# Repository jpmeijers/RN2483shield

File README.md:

# RN2483shield
KiCad design for a RN2483 shield for the Arduino Uno

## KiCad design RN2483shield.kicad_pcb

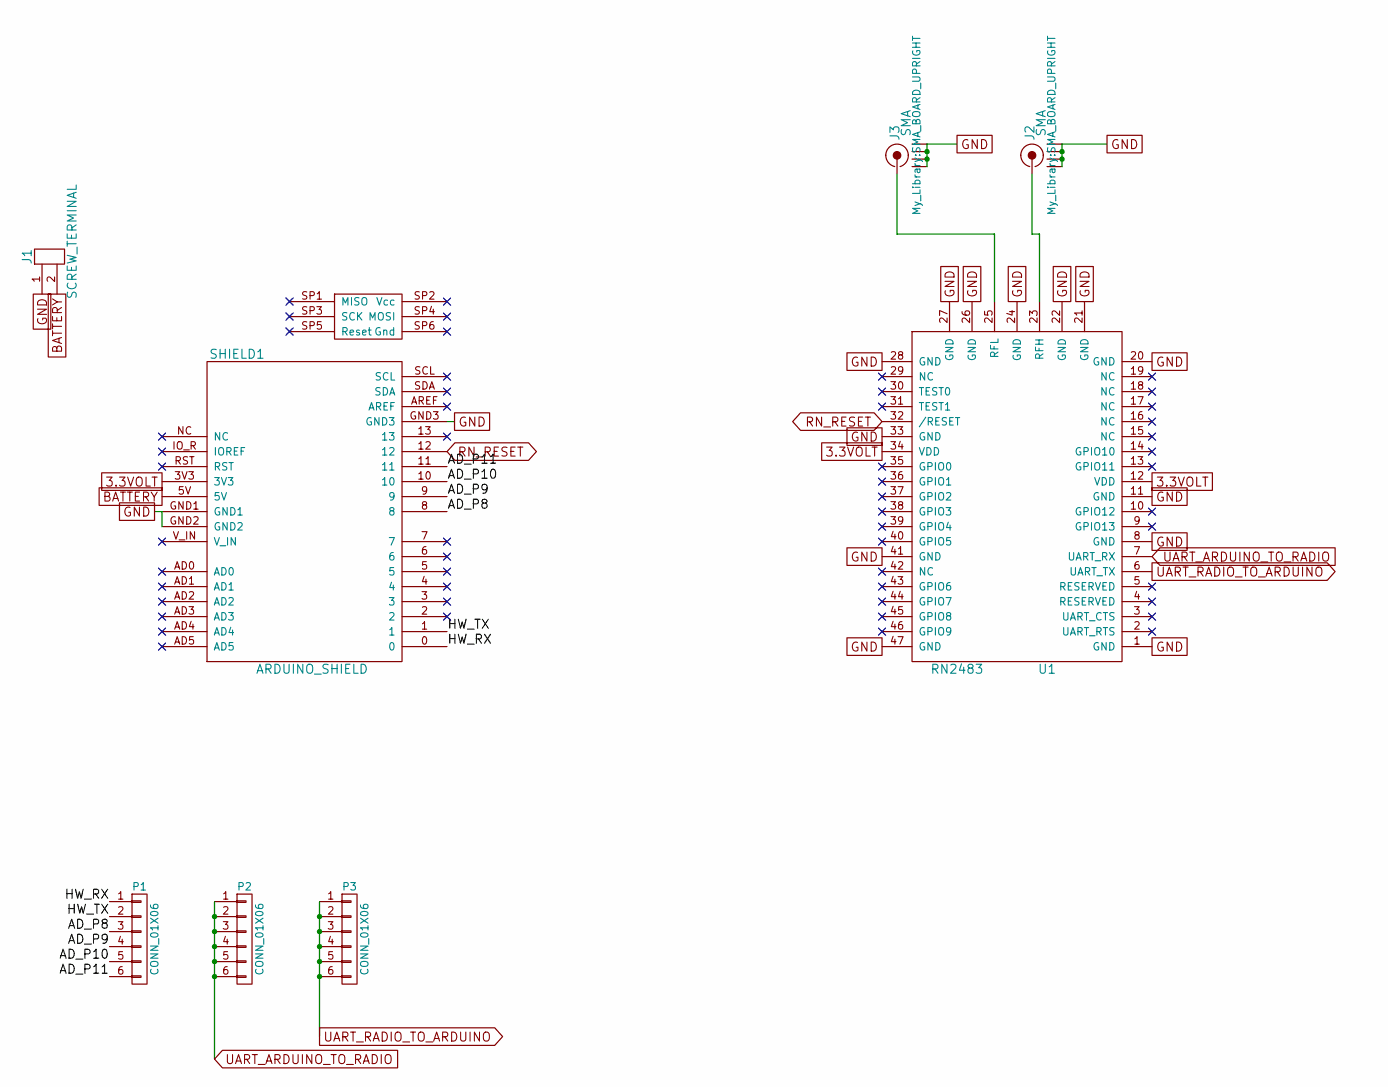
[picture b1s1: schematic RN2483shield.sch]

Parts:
J1: SCREW_TERMINAL; SCREWTERMINAL-5MM-2
J2, J3: SMA; SMA_BOARD_UPRIGHT
P1, P2, P3: CONN_01X06; Socket_Strip_Straight_1x06
SHIELD1: ARDUINO_SHIELD
U1: RN2483

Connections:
3.3VOLT: SHIELD1.3V3, U1.12 (VDD), U1.34 (VDD)
/AD_P8: P1.3, SHIELD1.8
/AD_P9: P1.4, SHIELD1.9
/AD_P10: P1.5, SHIELD1.10
/AD_P11: P1.6, SHIELD1.11
/HW_RX: P1.1, SHIELD1.0
/HW_TX: P1.2, SHIELD1.1
BATTERY: J1.2, SHIELD1.5V
GND: J1.1, J2.2 (GND1), J2.3 (GND2), J2.4 (GND3), J2.5 (GND4), J3.2 (GND1), J3.3 (GND2), J3.4 (GND3), J3.5 (GND4), SHIELD1.GND1, SHIELD1.GND2, SHIELD1.GND3, U1.1 (GND), U1.8 (GND), U1.11 (GND), U1.20 (GND), U1.21 (GND), U1.22 (GND), U1.24 (GND), U1.26 (GND), U1.27 (GND), U1.28 (GND), U1.33 (GND), U1.41 (GND), U1.47 (GND)
unnamed: J2.1 (RF), U1.23 (RFH)
unnamed: J3.1 (RF), U1.25 (RFL)
RN_RESET: SHIELD1.12, U1.32 (/RESET)
UART_ARDUINO_TO_RADIO: P2.1, P2.2, P2.3, P2.4, P2.5, P2.6, U1.7 (UART_RX)
UART_RADIO_TO_ARDUINO: P3.1, P3.2, P3.3, P3.4, P3.5, P3.6, U1.6 (UART_TX)

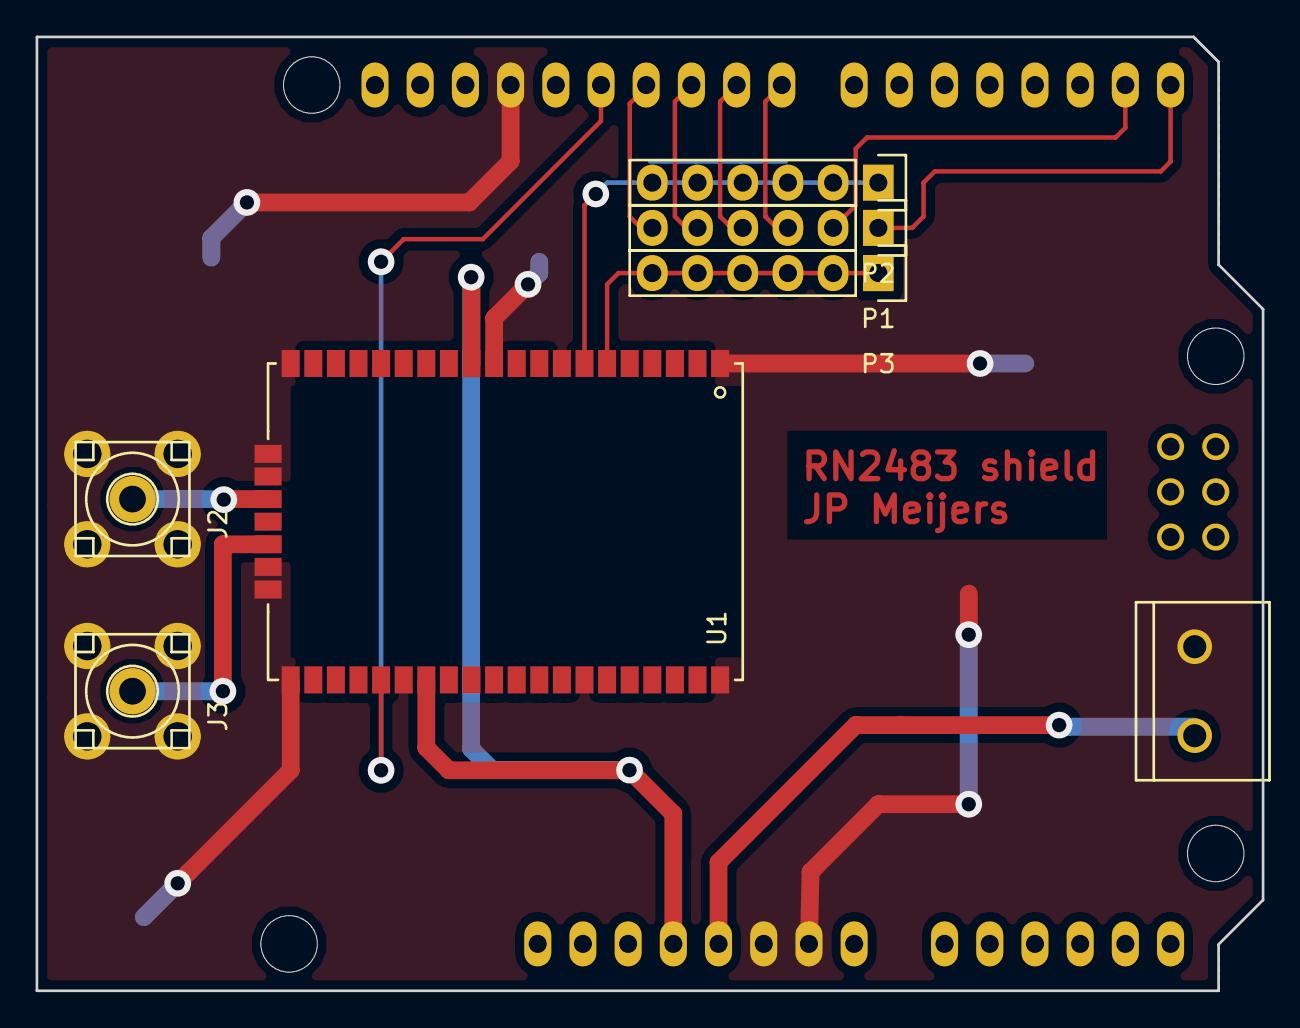
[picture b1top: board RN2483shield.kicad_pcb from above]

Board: 2 copper layers, 68.9 x 53.6 mm, 8 parts (0 on the bottom side), 14 nets.

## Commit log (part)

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2016-02-10 Version 2 of the PCB. Routed reset line to pin 12. Less possible UART pins.
2016-02-10 Cleaned up directory. Fixed libraries.
2016-02-10 More library include fixes. Polygon pour with thermal relief.
